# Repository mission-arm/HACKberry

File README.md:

We are going to update HACKberry bionic arm to the next level. https://github.com/mission-arm/HACKberry

We want to use most of the 3D parts but redefining the sensoric, electronics and software used in the original project

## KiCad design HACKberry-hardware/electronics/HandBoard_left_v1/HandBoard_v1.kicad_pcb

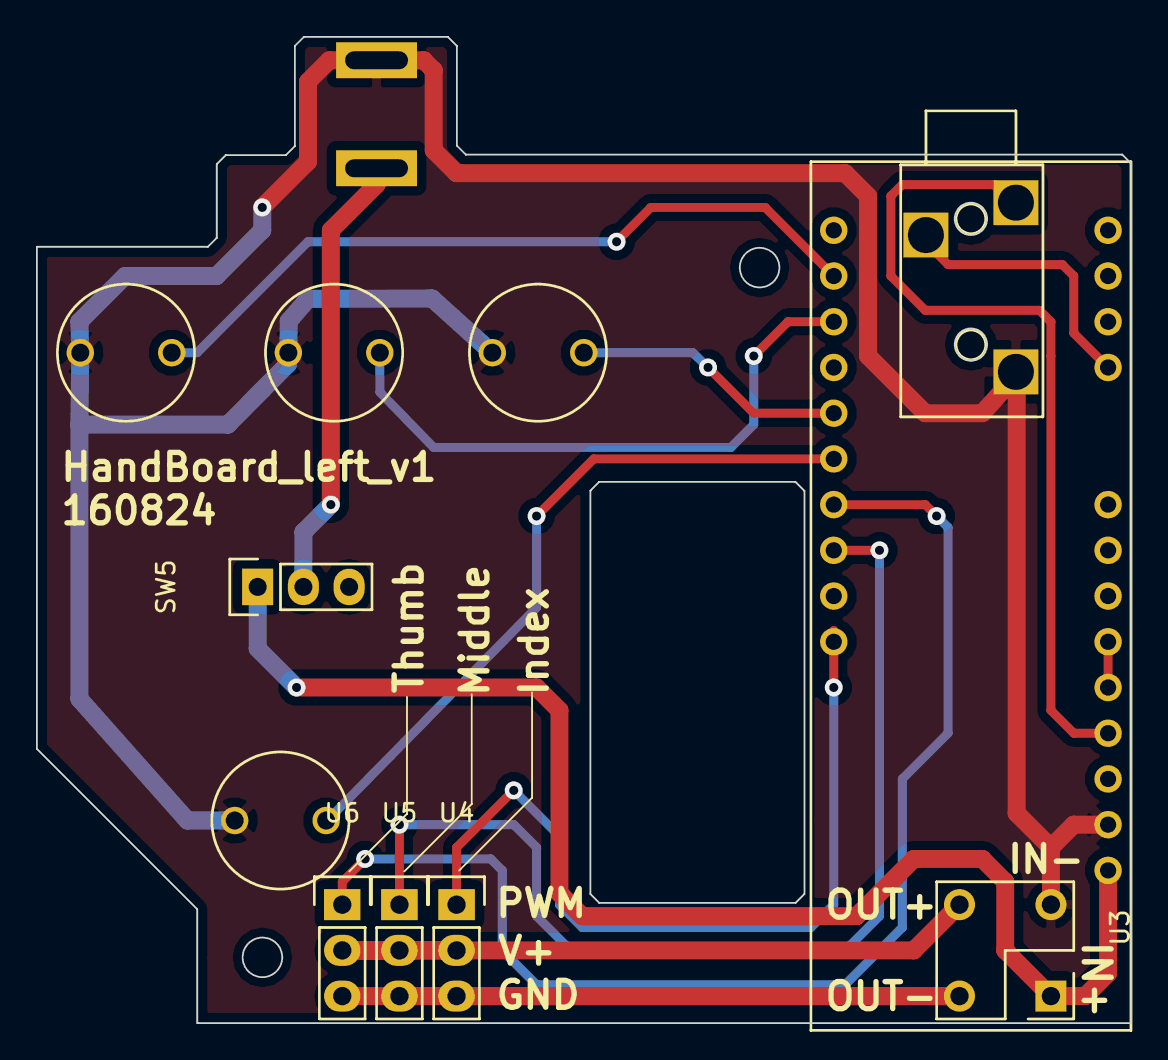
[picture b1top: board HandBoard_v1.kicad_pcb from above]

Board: 2 copper layers, 60.8 x 54.8 mm, 12 parts (0 on the bottom side), 14 nets.

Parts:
CON1: BARREL_JACK; MJ179PH
SW1:MAX1, SW2:MIN1, SW3:Thumb1, SW4:Middle1: SW_PUSH_SKRGAQD010; SKRGAQ0010
SW5: SWITCH_SS-12SDP2; Pin_Header_Straight_1x03
U1: 3-CONDUCTOR_MINIATUIRE_JACK_MJ-4535-3-RESCUE-Hand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; MINIATURE_JACK_MJ-4535-3
U2: Arduino_Micro
U3: Seed_Studio_Adjustable_DC/DC_Power_Converter_(1.2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; Pin_Header_Straight_2x02_Left_DCDC
U4: Servo_Motor_S03N; Pin_Header_Straight_1x03
U5, U6: Servo_Motor_ES08MD; Pin_Header_Straight_1x03

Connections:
/SW_MODE: SW3:Thumb1.2, U2.8
/SW_OPEN: SW2:MIN1.2, U2.10
/SW_PINCH: SW4:Middle1.2, U2.7
unnamed: CON1.1, SW5.2
unnamed: CON1.2, SW1:MAX1.1, SW2:MIN1.1, SW3:Thumb1.1, SW4:Middle1.1, U1.1, U2.GND, U3.2
unnamed: SW1:MAX1.2, U2.11
unnamed: SW5.1, U2.VIN, U3.1
unnamed: U1.2, U2.5V
unnamed: U1.4, U2.A0
unnamed: U2.3, U4.1
unnamed: U2.5, U5.1
unnamed: U2.6, U6.1
unnamed: U3.3, U4.3, U5.3, U6.3
unnamed: U3.4, U4.2, U5.2, U6.2

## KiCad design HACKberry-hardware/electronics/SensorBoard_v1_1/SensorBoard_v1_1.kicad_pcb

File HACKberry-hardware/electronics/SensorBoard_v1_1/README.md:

# Licenses
This sensor system is proposed by Japanese researchers Dr. Masahiro Yoshikawa et al.. exiii is using this method with their permission. For more detail, please see this proceedings.

Masahiro Yoshikawa, Yuya Taguchi, Shin Sakamoto, Shunji Yamanaka, Yoshio Matsumoto, Tsukasa Ogasawara, Noritaka Kawashima, “Trans-Radial Prosthesis with Three Opposed Fingers, ” IEEE/RSJ International Conference on Intelligent Robots and Systems (IROS2013), pp.1493-1498, Tokyo, Japan, Nov, 2013.

If you use the data, please use following credit.

Design:  
exiii  
CC BY-SA 4.0

Original design:  
M. Yoshikawa

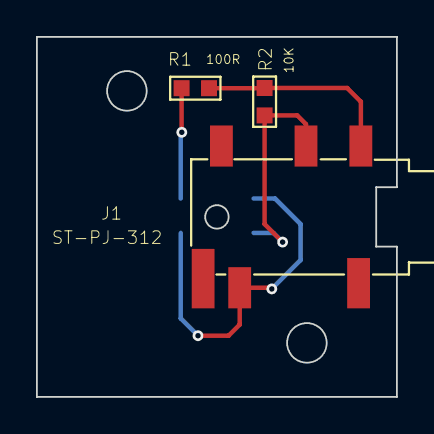
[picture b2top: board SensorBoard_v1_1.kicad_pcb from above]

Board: 2 copper layers, 20.0 x 20.0 mm, 4 parts (1 on the bottom side), 4 nets.

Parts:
J1: ST-PJ-312; SUNTECH_ST-PJ-312
R1: 100R; R0603
R2: 10K; R0603
U1: QRE1113GR; 4LEADSMD

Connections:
GND: J1.L, U1.E, U1.K
unnamed: J1.R, R2.1, U1.C
unnamed: R1.1, U1.A
VCC: J1.COM1, R1.2, R2.2

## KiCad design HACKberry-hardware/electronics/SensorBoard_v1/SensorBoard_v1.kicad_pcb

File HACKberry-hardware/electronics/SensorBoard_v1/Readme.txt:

SensorBoard_v1 is desinged for using PCB plotter and reflow soldering.

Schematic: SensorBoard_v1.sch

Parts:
R1: 10k; R_0603_HandSoldering
R2: 300; R_0603_HandSoldering
U1: 3-CONDUCTOR_MINIATUIRE_JACK_MJ-4535-3-RESCUE-Hand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; MINIATURE_JACK_MJ-4535-3
U2: TPR-105; TPR-105smd

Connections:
unnamed: R1.1, R2.1, U1.1
unnamed: R1.2, U1.4, U2.4 (Emitter)
unnamed: R2.2, U2.2 (Cathode)
unnamed: U1.2, U2.1 (Anode), U2.3 (Collector)

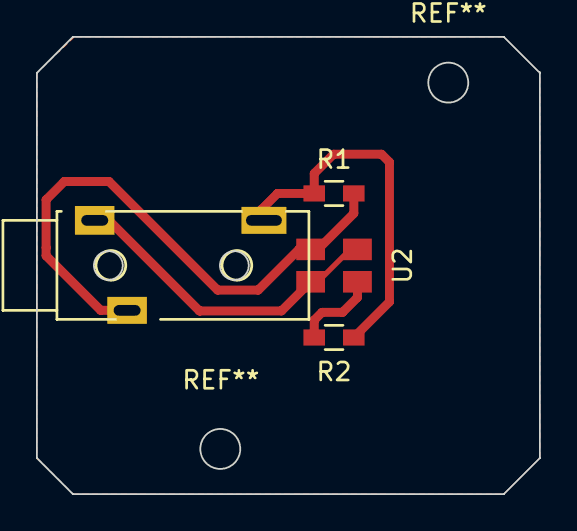
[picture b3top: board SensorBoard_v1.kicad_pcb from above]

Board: 2 copper layers, 27.9 x 25.4 mm, 4 parts (0 on the bottom side), 4 nets.

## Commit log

2015-05-17 first commit
    first commit
2015-05-18 test
    comment test
2015-05-20 hardwareTest1
    hardwareTest1
2015-05-20 test1
    test2
2015-05-20 uploadTest
2015-05-20 delete
2015-05-21 test
2015-05-21 test2
2015-05-21 refactored
2015-05-22 upload
2015-05-23 rivice of the schematic
    add the parts name of slide switch
2015-05-23 rivice of the README.md
2015-05-23 bug fix
2015-05-23 add
    upload the battery board data and sensor board data
2015-05-23 rivision of the README.md
2015-05-23 rivision of the policy
2015-05-25 Fixed minor formatting issues
2015-05-27 Fixed incorrect appearance in schematic
2015-05-29 Revert "Fixed incorrect appearance in schematic"
    This reverts commit 3b6817b660281c2eda156baa4225a43203330258.
2015-05-29 modify
2015-05-29 Revert "Revert "Fixed incorrect appearance in schematic""
    This reverts commit 5cdc5c46337e107bca08166c1673e08221bf1df3.
2015-05-29 Revert "modify"
    This reverts commit 7cc21e78040ca20a5a75b3f63a87baaadaba0b3a.
2015-05-29 Uploaded the Inventor data
2015-06-02 Deleted Files
2015-06-03 Upload STL files
2015-06-03 Upload BOM
2015-06-03 Modify the problem of thin-wall
2015-06-05 Added flat screws
2015-06-05 Added flat screw
2015-06-05 Added tension spring
2015-06-07 Modified the schematic.
    Added the push switch.
2015-06-07 Updated the schematic
2015-06-10 Fixed an error of SensorBoard schematic
    resistance values were not correct.
2015-06-14 Added presentation files
2015-06-25 Proceeded detail design of the hand boad
2015-06-30 Added README.md
    Licenses about the sensor system.
2015-06-30 Fixed minor miswriting
2015-07-03 made the garber data of the HandBoard_v1
2015-07-03 made the garber data of HandBoard_v1
    this data is not tested yet. I will make PCB using this data on July 7.
2015-07-21 test
    test
2015-07-21 Fixed english descriptions
2015-07-22 Fixed file error
2015-07-22 Updated the garber data of HandBoard_v1
2015-07-23 Updated the BOM
    Added the sensor parts to BOM list.
2015-07-29 Fixed index finger's interference
2015-07-29 Updated STL data
2015-07-30 Fixed minor error.
2015-07-30 Deleted a wrong link
2015-08-01 Added the update date.
2015-08-03 Added the link to a substitution of small servo motor
    Emax ES08MD
2015-08-05 Updated the substitution link of the battery.
2015-08-05 Deleted unnecessary libraries.
2015-08-05 Uploaded the 3D data of new socket
2015-08-11 Added garber data of SensorBoard
2015-08-11 Fixed minor error
2015-08-13 Fixed the error of Arduino_micro foot print
2015-08-22 Upgraded the strength of index finger
2015-08-22 Fixed reference problem of libraries.
2015-08-23 Fixed minor errors
2015-08-23 Fixed minor erroes
2015-08-26 Upgraded the shaft stoppers
2015-08-26 Updated the 3D data.
2015-09-06 Added minor errors of BOM
2015-09-06 Fixed minor problem of 3D data
2015-09-07 Upgraded the wrist part
    The wrist part (HbPalmBase03) is modified so that it can be attached
    both HACKberry's socket and conventional body-powered prosthesis.
2015-09-08 Added the images of PCB
2015-09-11 Started designing HandBoard_v2
2015-09-16 Fixed the error of the screw length
2015-09-16 Added the STL files of new socket
2015-09-16 Modified the mechanism of thumb.
    Added the manual joint to thumb. It enables users to change hand posture
    from pinching to grasping.
2015-09-17 Upload the STL data of pcb boards
2015-09-17 Modified the mechanism of thumb. 02
2015-09-27 Changed the small servo and fixed minor errors.
    Changed ASV-15MG to ES08MD.
2015-10-07 Added the url for a spring store
2015-10-07 Added STL data for left hand
2015-10-07 Simplified the structure of BatteryDoor and Added some parts data for left hand.
2015-10-08 Added Arduino sketch for left hand
2015-11-03 Updated the HandBoard
    changed the voltage for sensor from 3.3[V] to 5.0[V].
    modified the garber data for milling.
2015-11-03 Added the STL data for ledt hand.
2015-11-03 Modified the structure of the Battery Unit.
2015-11-06 Updated assembly files
2015-11-06 Updated the 3D data
    -Enlarged the clearance gaps between parts
    -Standardized the screws
2015-11-12 Updated BOM
2015-11-18 Updated the link of steel ball
2015-11-26 Uploaded the PCB files for manufacturing
2015-12-02 organezed the STL folder
2015-12-11 Fixed minor URL error
2015-12-14 Updated STP file.
2015-12-18 Added SensorBoard_v1_1
2015-12-19 Updated thumb mechanism.
2015-12-23 Added polygon data of HACKberry
    Polygonised by Yuji Yoshikai + Hiroshi Ishikawa
    This work is part of Kota Nezu's project.
2015-12-23 Changed the configuration of battery case
2016-01-04 Added README.md
2016-01-05 Apdated STEP and Parasolid files
2016-01-26 Updated the PCB files for PCB manufacturing service.
2016-01-28 Updated 3D data
    Modified features so that the parts can be printed with less support
    materials.
2016-01-28 Updated the BOM
2016-01-30 Added missing STL files
2016-02-02 Updated the terms of use.
2016-02-11 左手用メインボードを設計完了
2016-02-11 Updated Assembly data
    STEP, Parasolid, IGES
2016-02-11 Fixed minor error of HbPalmBase03
2016-02-12 Deleted unnecessary files.
2016-02-16 Fixed minnor mistakes of 3D data.
2016-02-17 Updated Sensor system.
    Added a plate which covers the sensor.
2016-02-18 Change DC-jack to PJ-102A
2016-02-19 Updated the problem of assmebling.
2016-02-21 Updated the BOM
    Added 3001HB as a substitution for S03N.
2016-02-23 Solved the problem of the HbPalmBase weakness.
2016-02-25 Add BOM for 3D printing service
2016-02-25 Make 3D Print1 assembly.
2016-02-25 Make 3D Print2 and 3 assembly
2016-02-25 Make 3D print4~7 assembly
2016-02-25 Update list of WristU's parts on BOM for printing.
2016-02-25 update assembly for print6 & 7
2016-02-25 Make assembly of all parts for printing
2016-02-25 add Case of parts
2016-02-25 Change pitch of mesh on PrintingCase
2016-02-25 Update thumb assembly
    reinforce the thumb
2016-02-26 Update thumb 3D data
    Reinforce the thumb structure
2016-02-29 Update the thumb data for left hand.
2016-03-02 change initial position of thumb for assembling
2016-03-02 Update HandBoard garber data for left hand
2016-03-09 Fix assembling problem
2016-03-16 Reinforce battery hinge
2016-03-24 enlarge diameter of prepared holes
    from 1.6 or 1.7 mm to 1.8mm. It will make assembling easy.
2016-03-24 Update 3D data
2016-03-29 Add vercro band for sensor unit to BOM list
2016-03-30 Reverse the value of sensor
2016-04-07 Update the 3D data
2016-04-07 Update the BOM
    add audio cable. correct some mistakes.
2016-04-07 Update inventor files
2016-04-07 correct some mistakes in BOM
2016-04-07 fixe interference of the finger
2016-04-08 correct the number of screw
2016-04-17 divide MainFrame!01 into two parts
2016-05-03 devide HbMainFrameA01 into two pieces
2016-05-03 divided MainFrameA into two pieces.
2016-05-06 change the number of screw in BOM
2016-05-10 update HbShaftStopperB to correct version.
2016-06-03 trial and error
2016-06-06 change the arrangement of pins and the size of DC-DC converter and rewire all routes.
2016-06-06 change the voltage to sensor to 5V
2016-06-10 make assemble file for SLS printing
2016-06-11 Update terms of use
2016-06-12 Fix minor formatting issues.
2016-06-15 added drill for eyephone jack
    added polygon for GND on buttom layer
    made garbar data
2016-06-17 add poly switch to protect servo motor
2016-06-17 modified texts and add polygon on internal layers
2016-07-10 replace servo motor S03N with HD3001HB
2016-08-24 pr/12
2016-08-24 Fix minor errors
2016-08-24 Fix the positions of switches.
2016-09-05 Fix minor name error
2016-09-05 Make small dent in to avoid collision between HBarmMountBaseCover03.ipt and HBabductionLever02.
2016-09-08 Reinforce the thumb unit.
2016-10-16 yuki.ogasawara
    2016/10/16_小笠原プログラム変更
2016-11-09 Reinforce the thumb unit 02
2017-01-04 Program fix
    Correction of rotation direction of servo motor of index finger
2017-04-26 add .gitignore for hardware directory
2017-04-26 change .gitignore
2017-09-02 Create Questions and remarks
2017-09-21 upgrade hardware, circuits and software to mk2
2017-09-21 add STL and STEP data for SLS print
2017-09-28 Update and sort the BOM file
2017-10-22 Rename directories
2017-11-28 add graps mode and serial num out
2017-12-13 シリアルナンバーの出力ができない問題の修正
2018-02-20 ボードのバージョンによる分岐を追加 サーボのピンとセンサーのピンを後で変更するようにした
2018-02-20 mk2のボタン仕様に対応(pullupのないpinがある)
2018-03-05 fix some interference
2018-04-25 add an arduino sketch for HACKberry Mk2.
2018-04-30 fix some bugs about button reading
2018-05-16 add arduino software for EMG
2018-06-29 add Reverse Button
2018-06-29 fix local variable initialization in Hackberryv3.0.ino
2018-08-19 fix hyper link for DCDC converter
2018-08-19 fix some error for compile
2026-02-01 TODO added
2026-02-02 new documentation
2026-02-03 new doc for 3d models
